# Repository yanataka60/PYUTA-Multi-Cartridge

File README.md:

# TOMY ぴゅう太用Multi Cartridge

　いぬふとさんがたくさんのレトロPC用自作プログラムを公開してくださっており、ぴゅう太用としてはROMイメージでの公開となっています。

　そこで実機で気楽に遊べるようROMイメージをディップスイッチで切り替えられるカートリッジを作ってみました。

　公開されているROMイメージには(>8000～)、(>4000～)の二種類があり、それぞれ(>8000～)用の16K(8K)ROM Multi Cartridgeと(4000～)用の32KROM Multi Cartridgeを使用します。

#### 注)32KROM Multi Cartridgeを初代ぴゅう太で使用するにはゲームアダプター相当品が必要です。初代ぴゅう太のカートリッジスロットに32KROM Multi Cartridgeを挿入しても動作しません。

　16K(8K)ROM Multi Cartridgeはぴゅう太、ぴゅう太mk2で動作確認、32KROM Multi Cartridgeはぴゅう太+ゲームアダプター相当品、ぴゅう太mk2で動作確認を行いましたが、ぴゅう太Jr.も両方とも動作すると思います。

　なお、当然ですがROMへ書き込むための機器が別途必要となります。

## 16K(8K)ROM Multi Cartridge
### 回路図
　KiCadフォルダ内のPYUTA16k.pdfを参照してください。

[回路図](https://github.com/yanataka60/PYUTA-Multi-Cartridge/blob/main/Kicad/16K/PYUTA16k.pdf)

### 部品
|番号|品名|数量|備考|
| ------------ | ------------ | ------------ | ------------ |
|U1-U4|ROM 27512|1～4|最大4個|
|U5|74LS138|1||
|U6|74LS32|1||
|SW1|DIPスイッチ 4P|1|秋月電子通商 EDS104SZなど|
|R1-R4|カーボン抵抗 10KΩ|4||
|C1-C4、C6、C7|積層セラミックコンデンサ 0.1uF|6||
|C5|電解コンデンサ 16v100uF|1||
||28P ICソケット|4||
||16P ICソケット|1|使用は任意|
||14P ICソケット|1|使用は任意|

### ROMへの書込み
　ROMイメージを27512の0000h、4000h、8000h、C000hを先頭アドレスとして書き込みます。

### ROMイメージの切り替え
　DIPスイッチ1番、2番スイッチで0000h、4000h、8000h、C000hのイメージの切り替え、DIPスイッチ3番、4番スイッチでROMを選択できます。

　最大16種類のROMイメージを切り替え可能です。

## 32KROM Multi Cartridge
### 回路図
　KiCadフォルダ内のPYUTA32k.pdfを参照してください。

[回路図](https://github.com/yanataka60/PYUTA-Multi-Cartridge/blob/main/Kicad/32K/PYUTA32k.pdf)

### 部品
|番号|品名|数量|備考|
| ------------ | ------------ | ------------ | ------------ |
|U1-U4|ROM 27512|1～4|最大4個|
|U5|74LS138|1||
|U6|74LS32|1||
|U7|74LS04|1||
|U8|74LS08|1||
|SW1|DIPスイッチ 4P|1|秋月電子通商 EDS104SZなど、3Pしか使っていないので3Pでも可|
|R2-R4|カーボン抵抗 10KΩ|3||
|C1-C4、C6-C9|積層セラミックコンデンサ 0.1uF|8||
|C5|電解コンデンサ 16v100uF|1||
||28P ICソケット|4||
||16P ICソケット|1|使用は任意|
||14P ICソケット|3|使用は任意|

### ROMへの書込み
　ROMイメージを27512の0000h、8000hを先頭アドレスとして書き込みます。

### ROMイメージの切り替え
　DIPスイッチ1番スイッチで0000h、8000hのイメージの切り替え、DIPスイッチ2番、3番スイッチでROMを選択できます。

　最大8種類のROMイメージを切り替え可能です。

## 謝辞
　たくさんのゲームを公開してくださっているいぬふと様、ありがとうございます。

　ぴゅう太の解析情報を公開してくださっているEnri様、ありがとうございます。

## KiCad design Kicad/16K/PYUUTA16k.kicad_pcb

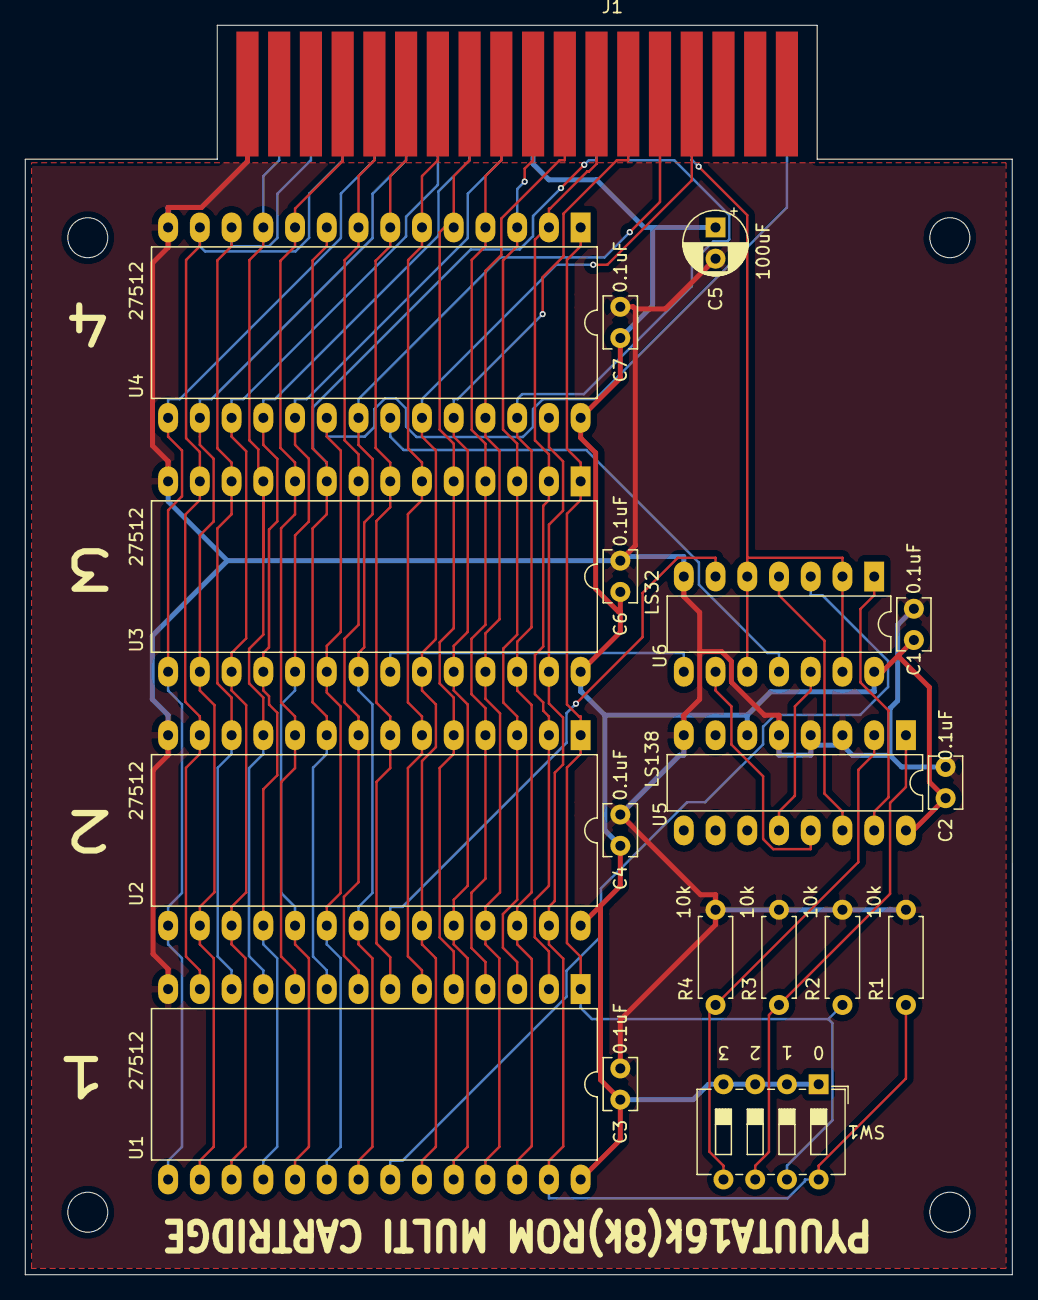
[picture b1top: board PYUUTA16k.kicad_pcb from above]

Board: 2 copper layers, 79.0 x 100.0 mm, 23 parts (0 on the bottom side), 38 nets.

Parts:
C1, C2, C3, C4, C6, C7: 0.1uF; C_Rect_L4.0mm_W2.5mm_P2.50mm
C5: 100uF; CP_Radial_D5.0mm_P2.50mm
J1: PYUUTA CART; BUS_36Pin
MH1, MH2, MH3, MH4: MountingHole_3.2mm_M3
R1, R2, R3, R4: 10k; R_Axial_DIN0207_L6.3mm_D2.5mm_P7.62mm_Horizontal
SW1: SW_DIP_x04; SW_DIP_SPSTx04_Slide_6.7x11.72mm_W7.62mm_P2.54mm_LowProfile
U1, U2, U3, U4: 27C512; DIP-28_W15.24mm_LongPads
U5: 74LS138; DIP-16_W7.62mm_LongPads
U6: 74LS32; DIP-14_W7.62mm_LongPads

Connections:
+5V: C1.1, C2.2, C3.2, C4.2, C5.1, C6.2, C7.2, J1.19, SW1.1, SW1.2, SW1.3, SW1.4, U1.28, U2.28, U3.28, U4.28, U5.6, U5.16, U6.14
/A2: J1.25, U1.26, U2.26, U3.26, U4.26
/A3: J1.24, U1.2, U2.2, U3.2, U4.2
/A4: J1.30, U1.23, U2.23, U3.23, U4.23
/A5: J1.28, U1.21, U2.21, U3.21, U4.21
/A6: J1.26, U1.24, U2.24, U3.24, U4.24
/A7: J1.22, U1.25, U2.25, U3.25, U4.25
/A8: J1.20, U1.3, U2.3, U3.3, U4.3
/A9: J1.18, U1.4, U2.4, U3.4, U4.4
/A10: J1.16, U1.5, U2.5, U3.5, U4.5
/A11: J1.14, U1.6, U2.6, U3.6, U4.6
/A12: J1.12, U1.7, U2.7, U3.7, U4.7
/A13: J1.10, U1.8, U2.8, U3.8, U4.8
/A14: J1.23, U1.9, U2.9, U3.9, U4.9
/A15: J1.8, U1.10, U2.10, U3.10, U4.10
/D0: J1.17, U1.19, U2.19, U3.19, U4.19
/D1: J1.15, U1.18, U2.18, U3.18, U4.18
/D2: J1.13, U1.17, U2.17, U3.17, U4.17
/D3: J1.11, U1.16, U2.16, U3.16, U4.16
/D4: J1.9, U1.15, U2.15, U3.15, U4.15
/D5: J1.7, U1.13, U2.13, U3.13, U4.13
/D6: J1.5, U1.12, U2.12, U3.12, U4.12
/D7: J1.3, U1.11, U2.11, U3.11, U4.11
/~CS0: J1.35, U1.20, U2.20, U3.20, U4.20
/~DBIN: J1.29, U6.2, U6.5, U6.10, U6.13
GND: C1.2, C2.1, C3.1, C4.1, C5.2, C6.1, C7.1, J1.1, J1.2, R1.2, R2.2, R3.2, R4.2, U1.14, U2.14, U3.14, U4.14, U5.3, U5.4, U5.5, U5.8, U6.7
unnamed: R1.1, SW1.8, U1.27, U2.27, U3.27, U4.27
unnamed: R2.1, SW1.7, U1.1, U2.1, U3.1, U4.1
unnamed: R3.1, SW1.6, U5.1
unnamed: R4.1, SW1.5, U5.2
unnamed: U1.22, U6.3
unnamed: U2.22, U6.6
unnamed: U3.22, U6.8
unnamed: U4.22, U6.11
unnamed: U5.12, U6.12
unnamed: U5.13, U6.9
unnamed: U5.14, U6.4
unnamed: U5.15, U6.1
